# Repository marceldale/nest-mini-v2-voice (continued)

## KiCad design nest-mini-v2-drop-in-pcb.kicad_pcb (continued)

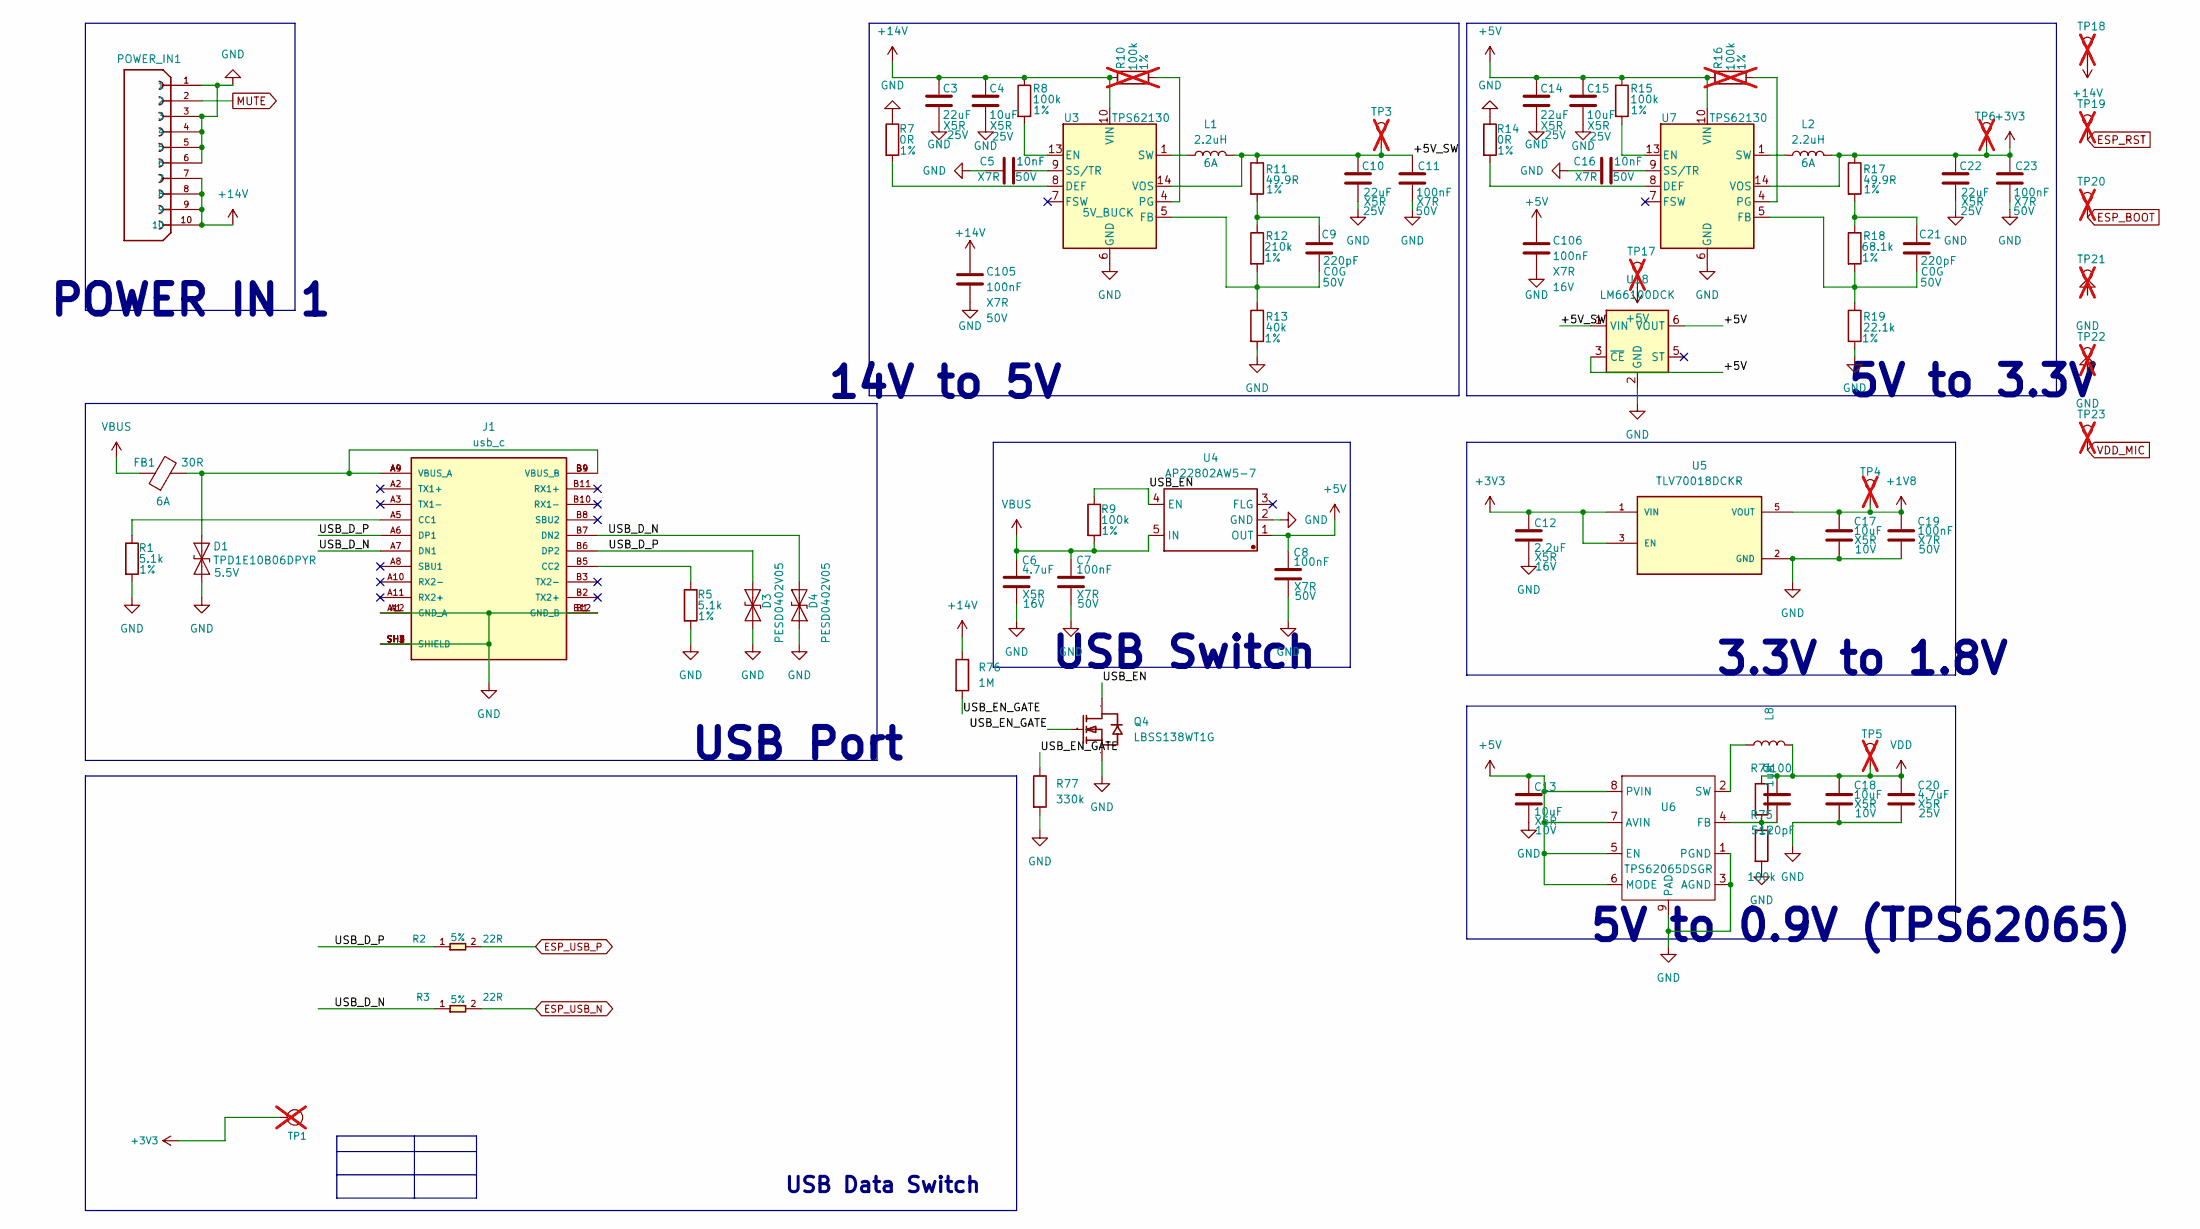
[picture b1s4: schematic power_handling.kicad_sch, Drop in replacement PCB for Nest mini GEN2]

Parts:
C3, C10, C14, C22: 22uF; C_0805_2012Metric; Voltage 25V; Manufacturer Part CL21A226MAQNNNE; LCSC Part # C45783
C4, C15: 10uF; C_0805_2012Metric; Voltage 25V; Manufacturer Part CL21A106KAYNNNE; LCSC Part # C15850
C5, C16: 10nF; C_0402_1005Metric; Voltage 50V; Manufacturer Part CL05B103KB5NNNC; LCSC Part # C15195
C6: 4.7uF; C_0603_1608Metric; Voltage 16V; Manufacturer Part CL10A475KO8NNNC; LCSC Part # C19666
C7, C8: 100nF; C_0603_1608Metric; Voltage 50V; Manufacturer Part CC0603KRX7R9BB104; LCSC Part # C14663
C9, C21: 220pF; C_0603_1608Metric; Voltage 50V; Manufacturer Part 0603CG221J500NT; LCSC Part # C156398
C11, C19, C23: 100nF; C_0805_2012Metric; Voltage 50V; Manufacturer Part CC0805KRX7R9BB104; LCSC Part # C49678
C12: 2.2uF; C_0603_1608Metric; Voltage 16V; Manufacturer Part CL10A225KO8NNNC; LCSC Part # C23630
C13, C17, C18: 10uF; C_0603_1608Metric; Voltage 10V; Manufacturer Part CL10A106KP8NNNC; LCSC Part # C19702
C20: 4.7uF; C_0805_2012Metric; Voltage 25V; Manufacturer Part CL21A475KAQNNNE; LCSC Part # C1779
C100: 120pF; C_0402_1005Metric; Voltage 50V; Manufacturer Part 0402CG121J500NT; LCSC Part # C40059
C105: 100nF; C_0402_1005Metric; Voltage 50V; Manufacturer Part CL05B104KB54PNC; LCSC Part # C307331
C106: 100nF; C_0402_1005Metric; Voltage 16V; Manufacturer Part CL05B104KO5NNNC; LCSC Part # C1525
D1: TPD1E10B06DPYR; TPD1E05U06DPYR; Voltage 5.5V; Manufacturer Part TPD1E10B06DPYR; LCSC Part # C48260
D3: PESD0402V05; D_0402_1005Metric; Part C19626254; LCSC Part # C19626254
D4: PESD0402V05; D_0402_1005Metric; Manufacturer Part PESD0402V05; LCSC Part # C19626254
FB1: 30R; R_0603_1608Metric; Part number BLM18PG300SN1D; LCSC Part # C17305
J1: usb_c; USB-C-SMD_TYPE-C-USB-18; Manufacturer Part 1054500101; LCSC Part # C134092
L1, L2: 2.2uH; L_Bourns_SRP4020TA; Manufacturer Part SRP4020TA-2R2M; LCSC Part # C719179
L8: 1uH; L_Murata_DFE201610P; Manufacturer Part WPN201610U1R0MTY01; LCSC Part # C395545
POWER_IN1: FH34SRJ-10S-0.5SH_50_; HRS_FH34SRJ-10S-0.5SH_50_; Manufacturer Part FH34SRJ-10S-0.5SH(50); LCSC Part # C324723
Q4: LBSS138WT1G; SOT-323_SC-70; Manufacturer Part LBSS138WT1G; LCSC Part # C383201
R1, R5: 5.1k; R_0402_1005Metric; Tolerance 1%; Manufacturer Part 0402WGF5101TCE; LCSC Part # C25905
R2, R3: 22R; R_0402_1005Metric; Tolerance 5%; MPN RC0402JR-0722RL; LCSC Part # C25092
R7, R14: 0R; R_0402_1005Metric; Tolerance 1%; Manufacturer Part 0402WGF0000TCE; LCSC Part # C17168
R8, R9, R15: 100k; R_0402_1005Metric; Tolerance 1%; Manufacturer Part 0402WGF1003TCE; LCSC Part # C25741
R10, R16: 100k; R_0402_1005Metric; Tolerance 1%; Manufacturer Part 0402WGJ0104TCE; LCSC Part # C25530; not fitted
R11, R17: 49.9R; R_0603_1608Metric; Tolerance 1%; Manufacturer Part 0603WAF499JT5E; LCSC Part # C23185
R12: 210k; R_0603_1608Metric; Tolerance 1%; Manufacturer Part 0603WAF2103T5E; LCSC Part # C22952
R13: 40k; R_0603_1608Metric; Tolerance 1%; Manufacturer Part RT0603BRD0740KL; LCSC Part # C861392
R18: 68.1k; R_0603_1608Metric; Tolerance 1%; Manufacturer Part 0603WAF6812T5E; LCSC Part # C25976
R19: 22.1k; R_0603_1608Metric; Tolerance 1%; Manufacturer Part 0603WAF2212T5E; LCSC Part # C25961
R74: 51k; R_0402_1005Metric; Manufacturer Part 0402WGF5102TCE; LCSC Part # C25794
R75: 100k; R_0402_1005Metric; Manufacturer Part 0402WGF1003TCE; LCSC Part # C25741
R76: 1M; R_0402_1005Metric; Manufacturer Part 0402WGF1004TCE; LCSC Part # C26083
R77: 330k; R_0402_1005Metric; Manufacturer Part 0402WGF3303TCE; LCSC Part # C25778
TP1, TP6: 3V3; TestPoint_Pad_D1.0mm; not fitted
TP3: 5V_SW; TestPoint_Pad_D1.0mm; not fitted
TP4: 1V8; TestPoint_Pad_D1.0mm; not fitted
TP5: VDD; TestPoint_Pad_D1.0mm; not fitted
TP17: 5V; TestPoint_Pad_D1.0mm; not fitted
TP18: 14V; TestPoint_Pad_D1.0mm; not fitted
TP19: RST; TestPoint_Pad_D1.0mm; not fitted
TP20: BOOT; TestPoint_Pad_D1.0mm; not fitted
TP21, TP22: GND; TestPoint_Pad_D1.0mm; not fitted
TP23: VMIC; TestPoint_Pad_D1.0mm; not fitted
U3, U7: TPS62130; VQFN-16-1EP_3x3mm_P0.5mm_EP1.68x1.68mm_ThermalVias; Manufacturer Part TPS62130ARGTR; LCSC Part # C337502
U4: AP22802AW5-7; SOT-23-5; Manufacturer Part AP22802AW5-7; LCSC Part # C211404
U5: TLV70018DCKR; SOT65P210X110-5N; PARTREV 3.1 - July 16, 2013; LCSC Part # C133796
U6: TPS62065DSGR; Texas_DSG0008A_WSON-8-1EP_2x2mm_P0.5mm_EP0.9x1.6mm; Manufacturer Part TPS62065DSGR; LCSC Part # C398352
U18: LM66100DCK; SOT-363_SC-70-6; Manufacturer Part LM66100DCKR; LCSC Part # C2869734

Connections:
+1V8: C17.1, C19.1, TP4.1, U5.5 (VOUT); also elsewhere on the board
+3V3: C12.1, C22.1, C23.1, L2.2, R17.1, TP1.1 (T), TP6.1, U5.1 (VIN), U5.3 (EN), U7.14 (VOS); also elsewhere on the board
+5V: C8.1, C13.1, C14.1, C15.1, C106.1, R15.1, R16.1, TP17.1, U4.1 (OUT), U6.5 (EN), U6.6 (MODE), U6.7 (AVIN), U6.8 (PVIN), U7.10 (VIN), U7.11 (VIN), U7.12 (VIN), U18.3 (~CE), U18.6 (VOUT); also elsewhere on the board
+14V: C3.1, C4.1, C105.1, POWER_IN1.7, POWER_IN1.8, POWER_IN1.9, POWER_IN1.10, R8.1, R10.1, R76.1, TP18.1, U3.10 (VIN), U3.11 (VIN), U3.12 (VIN); also elsewhere on the board
/Power/+5V_SW: C10.1, C11.1, L1.2, R11.1, TP3.1, U3.14 (VOS), U18.1 (VIN)
/Power/USB_D_N: D4.2 (A2), J1.A7 (DN1), J1.B7 (DN2), R3.1
/Power/USB_D_P: D3.2 (A2), J1.A6 (DP1), J1.B6 (DP2), R2.1
/Power/USB_EN: Q4.3 (D), R9.1, U4.4 (EN)
/Power/USB_EN_GATE: Q4.1 (G), R76.2, R77.1
ESP_BOOT: TP20.1; also elsewhere on the board
ESP_RST: TP19.1; also elsewhere on the board
ESP_USB_N: R3.2; also elsewhere on the board
ESP_USB_P: R2.2; also elsewhere on the board
GND: C3.2, C4.2, C5.1, C6.2, C7.2, C8.2, C10.2, C11.2, C12.2, C13.2, C14.2, C15.2, C16.1, C17.2, C18.2, C19.2, C20.2, C22.2, C23.2, C105.2, C106.2, D1.1 (A1), D3.1 (A1), D4.1 (A1), J1.A1 (GND_A), J1.A12 (GND_A), J1.B1 (GND_B), J1.B12 (GND_B), J1.SH1 (SHIELD), J1.SH2 (SHIELD), J1.SH3 (SHIELD), J1.SH4 (SHIELD), POWER_IN1.1, POWER_IN1.3, POWER_IN1.4, POWER_IN1.5, POWER_IN1.6, Q4.2 (S), R1.2, R5.2, R7.1, R13.2, R14.1, R19.2, R75.2, R77.2, TP21.1, TP22.1, U3.6 (GND), U3.15 (GND), U3.16 (GND), U3.17 (GND), U4.2 (GND), U5.2 (GND), U6.1 (PGND), U6.3 (AGND), U6.9 (PAD), U7.6 (GND), U7.15 (GND), U7.16 (GND), U7.17 (GND), U18.2 (GND); also elsewhere on the board
MUTE: POWER_IN1.2; also elsewhere on the board
unnamed: C9.1, R11.2, R12.1
unnamed: C21.1, R17.2, R18.1
unnamed: D1.2 (A2), FB1.2, J1.A4 (VBUS_A), J1.A9 (VBUS_A), J1.B4 (VBUS_B), J1.B9 (VBUS_B)
unnamed: J1.A5 (CC1), R1.1
unnamed: J1.B5 (CC2), R5.1
unnamed: L1.1, U3.1 (SW), U3.2 (SW), U3.3 (SW)
unnamed: L2.1, U7.1 (SW), U7.2 (SW), U7.3 (SW)
unnamed: R7.2, U3.8 (DEF)
unnamed: R8.2, U3.13 (EN)
unnamed: C9.2, R12.2, R13.1, U3.5 (FB)
unnamed: R10.2, U3.4 (PG)
unnamed: C5.2, U3.9 (SS/TR)
unnamed: C100.2, R74.2, R75.1, U6.4 (FB)
unnamed: L8.1, U6.2 (SW)
unnamed: R14.2, U7.8 (DEF)
unnamed: R15.2, U7.13 (EN)
unnamed: C21.2, R18.2, R19.1, U7.5 (FB)
unnamed: R16.2, U7.4 (PG)
unnamed: C16.2, U7.9 (SS/TR)
VBUS: C6.1, C7.1, FB1.1, R9.2, U4.5 (IN); also elsewhere on the board
VDD: C18.1, C20.1, C100.1, L8.2, R74.1, TP5.1; also elsewhere on the board
VDD_MIC: TP23.1; also elsewhere on the board

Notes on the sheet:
USB Port
POWER IN 1
14V to 5V
USB Switch
USB Data Switch
3.3V to 1.8V
5V to 3.3V
5V to 0.9V (TPS62065)

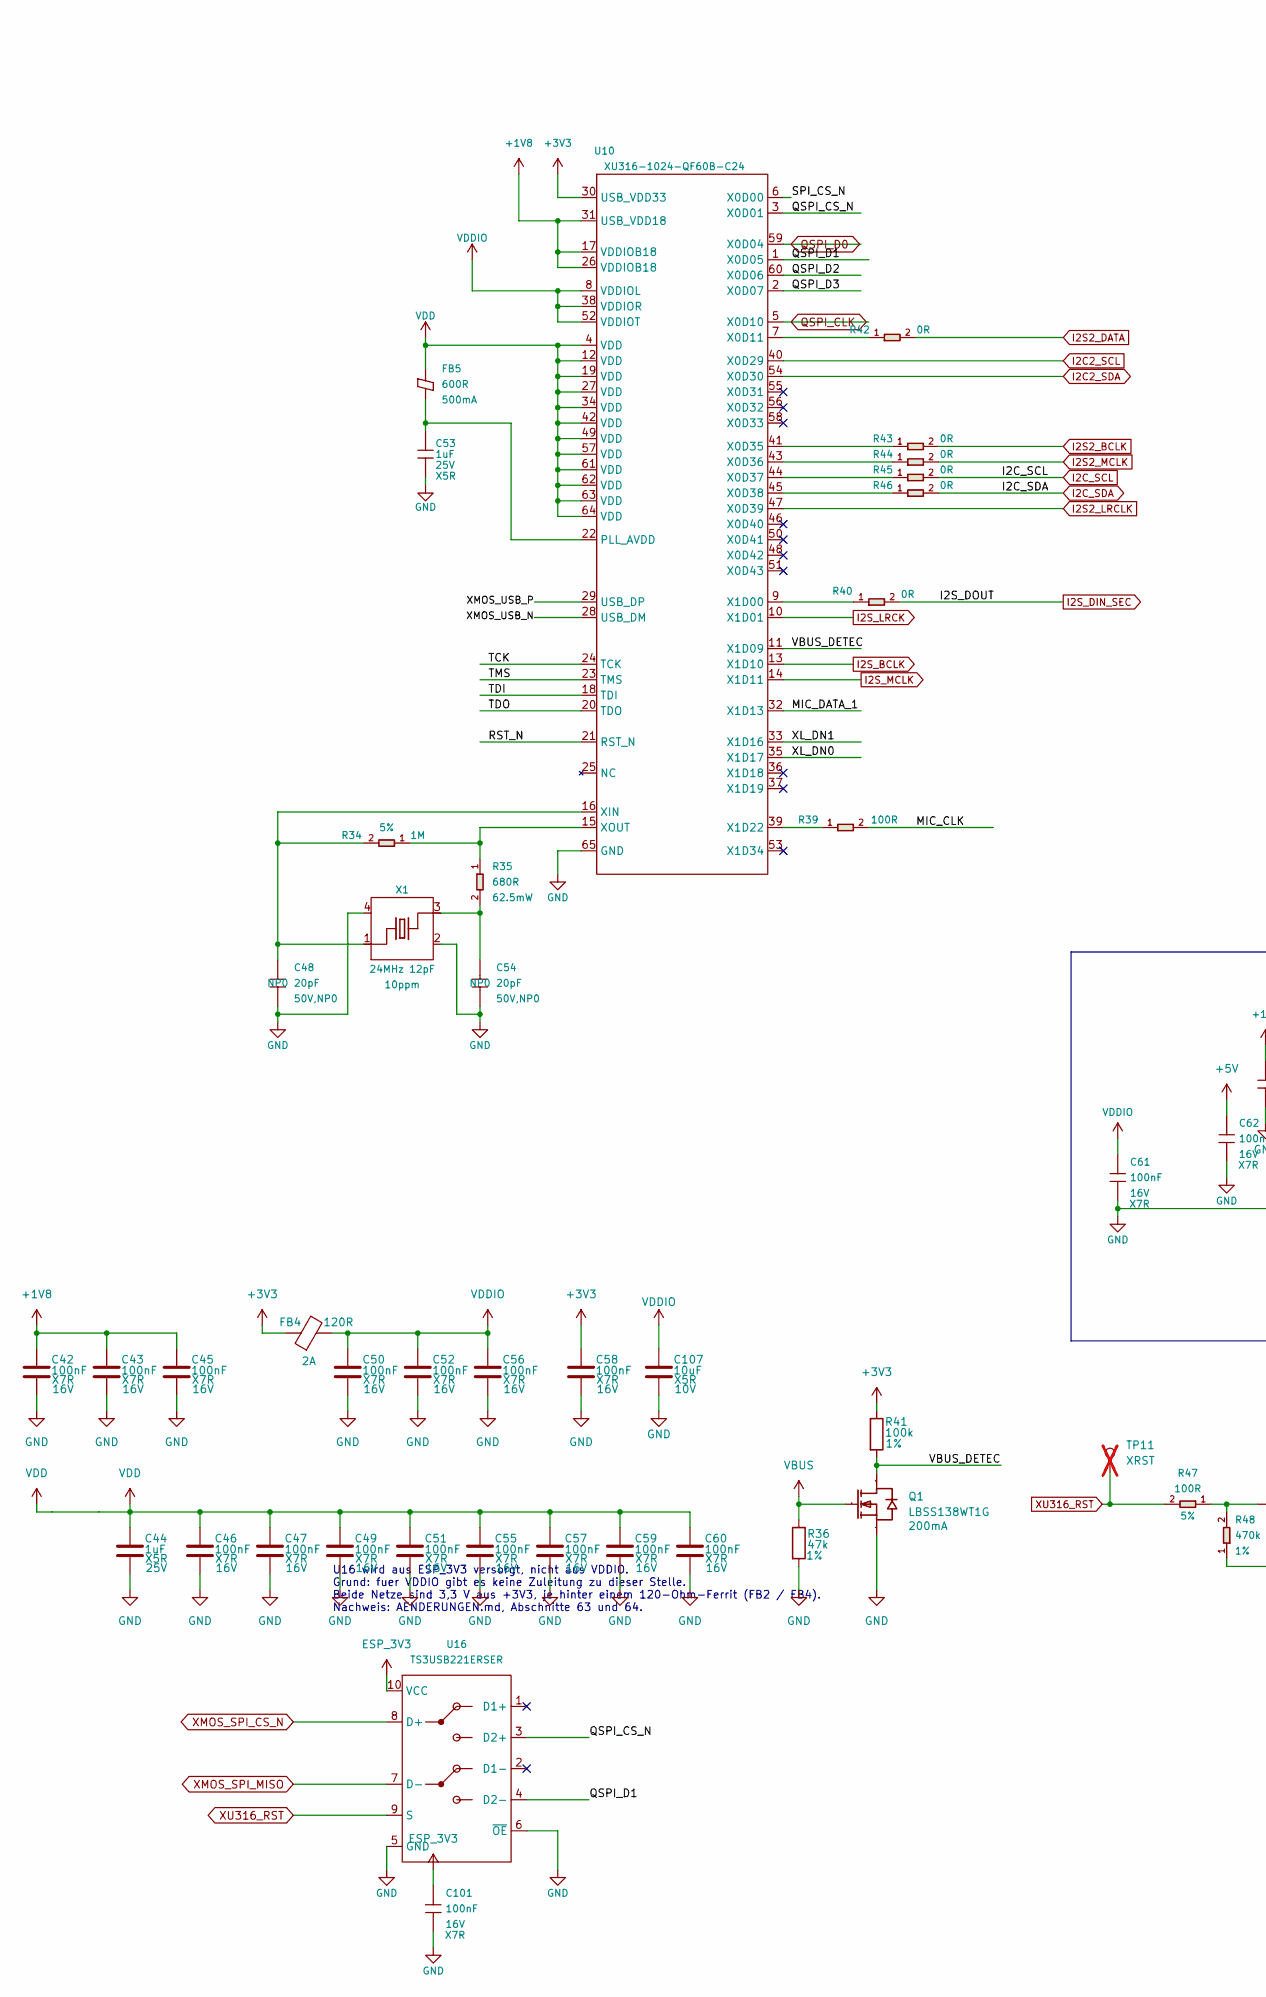
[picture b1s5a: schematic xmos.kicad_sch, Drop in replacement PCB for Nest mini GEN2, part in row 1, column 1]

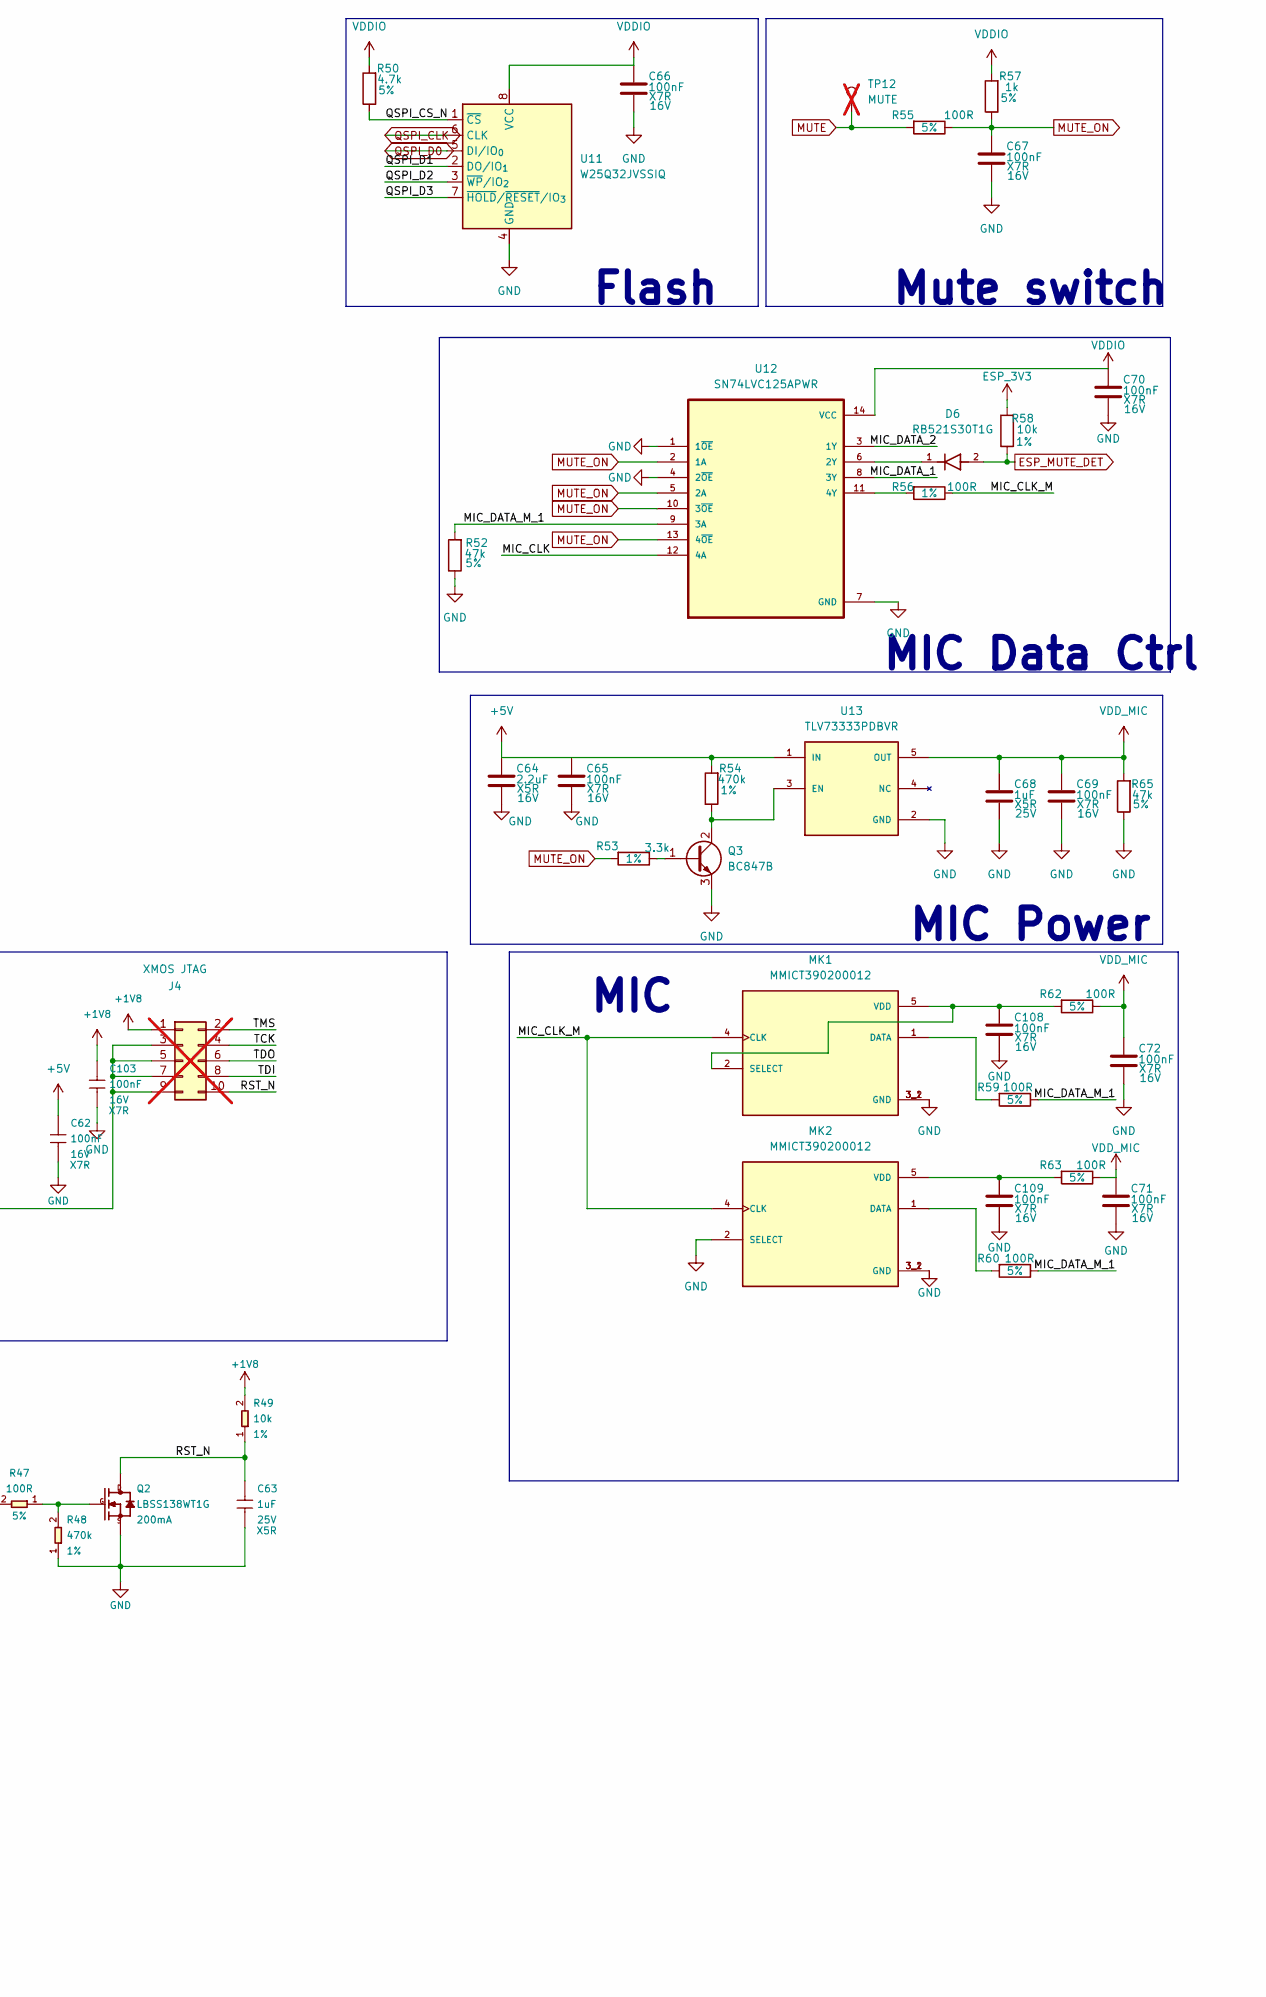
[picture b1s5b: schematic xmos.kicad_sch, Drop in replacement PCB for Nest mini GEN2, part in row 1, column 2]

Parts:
C42, C43, C45, C46, C47, C49, C50, C51, C52, C55, C56, C57, C58, C59, C60, C65, C66, C67, C69, C70, C71, C72, C108, C109: 100nF; C_0402_1005Metric; Voltage 16V; Manufacturer Part CL05B104KO5NNNC; LCSC Part # C1525
C44, C68: 1uF; C_0402_1005Metric; Voltage 25V; Manufacturer Part CL05A105KA5NQNC; LCSC Part # C52923
C48, C54: 20pF; C_0402_1005Metric; Voltage Rating 50V,NP0; Voltage 50V; MPN 0402CG200J500NT; LCSC Part # C1554
C53: 1uF; C_0402_1005Metric; Voltage Rating 25V; Voltage 25V; MPN CL05A105KA5NQNC; LCSC Part # C52923
C61, C62: 100nF; C_0402_1005Metric; Voltage Rating 16V; Voltage 16V; MPN CL05B104KO5NNNC; LCSC Part # C1525
C63: 1uF; C_0402_1005Metric; Voltage Rating 25V; MPN CL05A105KA5NQNC; LCSC Part # C52923
C64: 2.2uF; C_0603_1608Metric; Voltage 16V; Manufacturer Part CL10A225KO8NNNC; LCSC Part # C23630
C101, C103: 100nF; C_0402_1005Metric; Voltage Rating 16V; MPN CL05B104KO5NNNC; LCSC Part # C1525
C107: 10uF; C_0603_1608Metric; Voltage 10V; Manufacturer Part CL10A106KP8NNNC; LCSC Part # C19702
D6: RB521S30T1G; DIOM168X70N; PARTREV 7/11/1905; LCSC Part # C27636108
FB4: 120R; BLM18PG121SN1D; Part number BLM18AG121SN1D; LCSC Part # C14709
FB5: 600R; BLM18PG121SN1D; Rating 500mA; MPN BLM18KG601SN1D; LCSC Part # C85833
J4: XMOS JTAG; xSYS2_2x05_P1.27mm_Pads; not fitted
MK1, MK2: MMICT390200012; MIC_T3902; PARTREV 1.0; LCSC Part # C3171752
Q1: LBSS138WT1G; SC-70-3_L2.1-W1.3-P0.65-LS2.1-BR; Manufacturer Part LBSS138WT1G; LCSC Part # C383201
Q2: LBSS138WT1G; SOT-323_SC-70; Rating 200mA; MPN LBSS138WT1G; LCSC Part # C383201
Q3: BC847B; SOT-23; Manufacturer Part BC847B; LCSC Part # C20069135
R34: 1M; R_0402_1005Metric; Power Rating 5%; MPN 0402WGF1004TCE; LCSC Part # C26083
R35: 680R; R_0402_1005Metric; Power Rating 62.5mW; MPN CR0402FF6800G; LCSC Part # C100510
R36: 47k; R_0402_1005Metric; Tolerance 1%; Manufacturer Part 0402WGF4702TCE; LCSC Part # C25792
R39: 100R; R_0402_1005Metric; Power Rating 5%; MPN 0402WGF1000TCE; LCSC Part # C25076
R40, R43, R44, R45, R46: 0R; R_0402_1005Metric; Power Rating 5%; MPN 0402WGF0000TCE; LCSC Part # C17168
R41: 100k; R_0402_1005Metric; Tolerance 1%; Manufacturer Part 0402WGF1003TCE; LCSC Part # C25741
R42: 0R; R_0402_1005Metric; Tolerance 5%; MPN 0402WGF0000TCE; LCSC Part # C17168
R47: 100R; R_0402_1005Metric; Power Rating 5%; MPN RC0402JR-07100RL; LCSC Part # C25076
R48: 470k; R_0402_1005Metric; Power Rating 1%; MPN RC0402FR-07470KL; LCSC Part # C25790
R49: 10k; R_0402_1005Metric; Power Rating 1%; MPN RC0402FR-0710KL; LCSC Part # C25744
R50: 4.7k; R_0402_1005Metric; Tolerance 5%; Manufacturer Part 0402WGF4701TCE; LCSC Part # C25900
R52, R65: 47k; R_0402_1005Metric; Tolerance 5%; Manufacturer Part 0402WGF4702TCE; LCSC Part # C25792
R53: 3.3k; R_0402_1005Metric; Tolerance 1%; Manufacturer Part 0402WGF3301TCE; LCSC Part # C25890
R54: 470k; R_0402_1005Metric; Tolerance 1%; Manufacturer Part 0402WGF4703TCE; LCSC Part # C25790
R55, R59, R60, R62, R63: 100R; R_0402_1005Metric; Tolerance 5%; Manufacturer Part 0402WGF1000TCE; LCSC Part # C25076
R56: 100R; R_0402_1005Metric; Tolerance 1%; Manufacturer Part 0402WGF1000TCE; LCSC Part # C25076
R57: 1k; R_0402_1005Metric; Tolerance 5%; Manufacturer Part 0402WGF1001TCE; LCSC Part # C11702
R58: 10k; R_0402_1005Metric; Tolerance 1%; Manufacturer Part 0402WGF1002TCE; LCSC Part # C25744
TP11: XRST; TestPoint_Pad_D1.0mm; not fitted
TP12: MUTE; TestPoint_Pad_D1.0mm; not fitted
U10: XU316-1024-QF60B-C24; MPN XU316-1024-QF60B-C24; LCSC Part # C6617472
U11: W25Q32JVSSIQ; SOIC-8_5.3x5.3mm_P1.27mm; Manufacturer Part W25Q32JVSSIQ; LCSC Part # C179173
U12: SN74LVC125APWR; SOP65P640X120-14N; Manufacturer Part SN74LVC125APWR; LCSC Part # C7813
U13: TLV73333PDBVR; PARTREV C; LCSC Part # C134139
U16: TS3USB221ERSER; MPN TS3USB221ERSER; LCSC Part # C129313
X1: 24MHz 12pF; X4-SMD-2.0X1.6MM; Rating 10ppm; MPN 7F24000E12UCG; LCSC Part # C252273

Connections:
+1V8: C42.1, C43.1, C45.1, C103.1, J4.1, R49.2, U10.17 (VDDIOB18), U10.26 (VDDIOB18), U10.31 (USB_VDD18); also elsewhere on the board
+3V3: C58.1, FB4.1, R41.1, U10.30 (USB_VDD33); also elsewhere on the board
+5V: C62.1, C64.1, C65.1, R54.2, U13.1 (IN); also elsewhere on the board
/XMOS/MIC_CLK: R39.2, U12.12 (4A)
/XMOS/MIC_CLK_M: MK1.4 (CLK), MK2.4 (CLK), R56.1
/XMOS/MIC_DATA_1: U10.32 (X1D13), U12.8 (3Y)
/XMOS/MIC_DATA_2: U12.3 (1Y)
/XMOS/MIC_DATA_M_1: R52.2, R59.1, R60.1, U12.9 (3A)
/XMOS/QSPI_CS_N: R50.1, U10.3 (X0D01), U11.1 (~CS), U16.3 (D2+)
/XMOS/QSPI_D1: U10.1 (X0D05), U11.2 (DO/IO_{1}), U16.4 (D2-)
/XMOS/QSPI_D2: U10.60 (X0D06), U11.3 (~WP/IO_{2})
/XMOS/QSPI_D3: U10.2 (X0D07), U11.7 (~HOLD/~RESET/IO_{3})
/XMOS/RST_N: C63.1, J4.10, Q2.3 (D), R49.1, U10.21 (RST_N)
/XMOS/SPI_CS_N: U10.6 (X0D00)
/XMOS/TCK: J4.4, U10.24 (TCK)
/XMOS/TDI: J4.8, U10.18 (TDI)
/XMOS/TDO: J4.6, U10.20 (TDO)
/XMOS/TMS: J4.2, U10.23 (TMS)
/XMOS/VBUS_DETEC: Q1.3 (D), R41.2, U10.11 (X1D09)
/XMOS/XL_DN0: U10.35 (X1D17)
/XMOS/XL_DN1: U10.33 (X1D16)
/XMOS/XMOS_USB_N: U10.28 (USB_DM)
/XMOS/XMOS_USB_P: U10.29 (USB_DP)
ESP_3V3: C101.1, R58.2, U16.10 (VCC); also elsewhere on the board
ESP_MUTE_DET: D6.2, R58.1; also elsewhere on the board
GND: C42.2, C43.2, C44.2, C45.2, C46.2, C47.2, C48.2, C49.2, C50.2, C51.2, C52.2, C53.2, C54.2, C55.2, C56.2, C57.2, C58.2, C59.2, C60.2, C61.2, C62.2, C63.2, C64.2, C65.2, C66.2, C67.2, C68.2, C69.2, C70.2, C71.2, C72.2, C101.2, C103.2, C107.2, C108.2, C109.2, J4.3, J4.5, J4.7, J4.9, MK1.3_1 (GND), MK1.3_2 (GND), MK2.2 (SELECT), MK2.3_1 (GND), MK2.3_2 (GND), Q1.2 (S), Q2.2 (S), Q3.3 (E), R36.2, R48.1, R52.1, R65.1, U10.65 (GND), U11.4 (GND), U12.1 (1~OE), U12.4 (2~OE), U12.7 (GND), U13.2 (GND), U16.5 (GND), U16.6 (~OE), X1.2, X1.4; also elsewhere on the board
I2C2_SCL: U10.40 (X0D29)
I2C2_SDA: U10.54 (X0D30)
I2C_SCL: R45.2; also elsewhere on the board
I2C_SDA: R46.2; also elsewhere on the board
I2S2_BCLK: R43.2; also elsewhere on the board
I2S2_DATA: R42.2; also elsewhere on the board
I2S2_LRCLK: U10.47 (X0D39); also elsewhere on the board
I2S2_MCLK: R44.2; also elsewhere on the board
I2S_BCLK: U10.13 (X1D10); also elsewhere on the board
I2S_DIN_SEC: R40.2; also elsewhere on the board
I2S_LRCK: U10.10 (X1D01); also elsewhere on the board
I2S_MCLK: U10.14 (X1D11); also elsewhere on the board
MUTE: R55.2, TP12.1; also elsewhere on the board
MUTE_ON: C67.1, R53.2, R55.1, R57.1, U12.2 (1A), U12.5 (2A), U12.10 (3~OE), U12.13 (4~OE)
unnamed: C54.1, R35.2, X1.3
unnamed: MK1.1 (DATA), R59.2
unnamed: C108.1, MK1.2 (SELECT), MK1.5 (VDD), R62.2
unnamed: MK2.1 (DATA), R60.2
unnamed: C109.1, MK2.5 (VDD), R63.2
unnamed: Q2.1 (G), R47.1, R48.2
unnamed: Q3.1 (B), R53.1
unnamed: Q3.2 (C), R54.1, U13.3 (EN)
unnamed: C53.1, FB5.1, U10.22 (PLL_AVDD)
unnamed: R42.1, U10.7 (X0D11)
unnamed: R43.1, U10.41 (X0D35)
unnamed: R44.1, U10.43 (X0D36)
unnamed: R45.1, U10.44 (X0D37)
unnamed: R46.1, U10.45 (X0D38)
unnamed: R40.1, U10.9 (X1D00)
unnamed: R39.1, U10.39 (X1D22)
unnamed: C48.1, R34.2, U10.16 (XIN), X1.1
unnamed: R34.1, R35.1, U10.15 (XOUT)
unnamed: D6.1, U12.6 (2Y)
unnamed: R56.2, U12.11 (4Y)
QSPI_CLK: U10.5 (X0D10), U11.6 (CLK); also elsewhere on the board
QSPI_D0: U10.59 (X0D04), U11.5 (DI/IO_{0}); also elsewhere on the board
VBUS: Q1.1 (G), R36.1; also elsewhere on the board
VDD: C44.1, C46.1, C47.1, C49.1, C51.1, C55.1, C57.1, C59.1, C60.1, FB5.2, U10.4 (VDD), U10.12 (VDD), U10.19 (VDD), U10.27 (VDD), U10.34 (VDD), U10.42 (VDD), U10.49 (VDD), U10.57 (VDD), U10.61 (VDD), U10.62 (VDD), U10.63 (VDD), U10.64 (VDD); also elsewhere on the board
VDDIO: C50.1, C52.1, C56.1, C61.1, C66.1, C70.1, C107.1, FB4.2, R50.2, R57.2, U10.8 (VDDIOL), U10.38 (VDDIOR), U10.52 (VDDIOT), U11.8 (VCC), U12.14 (VCC)
VDD_MIC: C68.1, C69.1, C71.1, C72.1, R62.1, R63.1, R65.2, U13.5 (OUT); also elsewhere on the board
XMOS_SPI_CS_N: U16.8 (D+); also elsewhere on the board
XMOS_SPI_MISO: U16.7 (D-); also elsewhere on the board
XU316_RST: R47.2, TP11.1, U16.9 (S); also elsewhere on the board

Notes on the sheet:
Flash
MIC
Mute switch
MIC Power
MIC Data Ctrl
U16 wird aus ESP_3V3 versorgt, nicht aus VDDIO. Grund: fuer VDDIO gibt es keine Zuleitung zu dieser Stelle. Beide Netze sind 3,3 V aus +3V3, je hinter einem 120-Ohm-Ferrit (FB2 / FB4). Nachweis: AENDERUNGEN.md, Abschnitte 63 und 64.

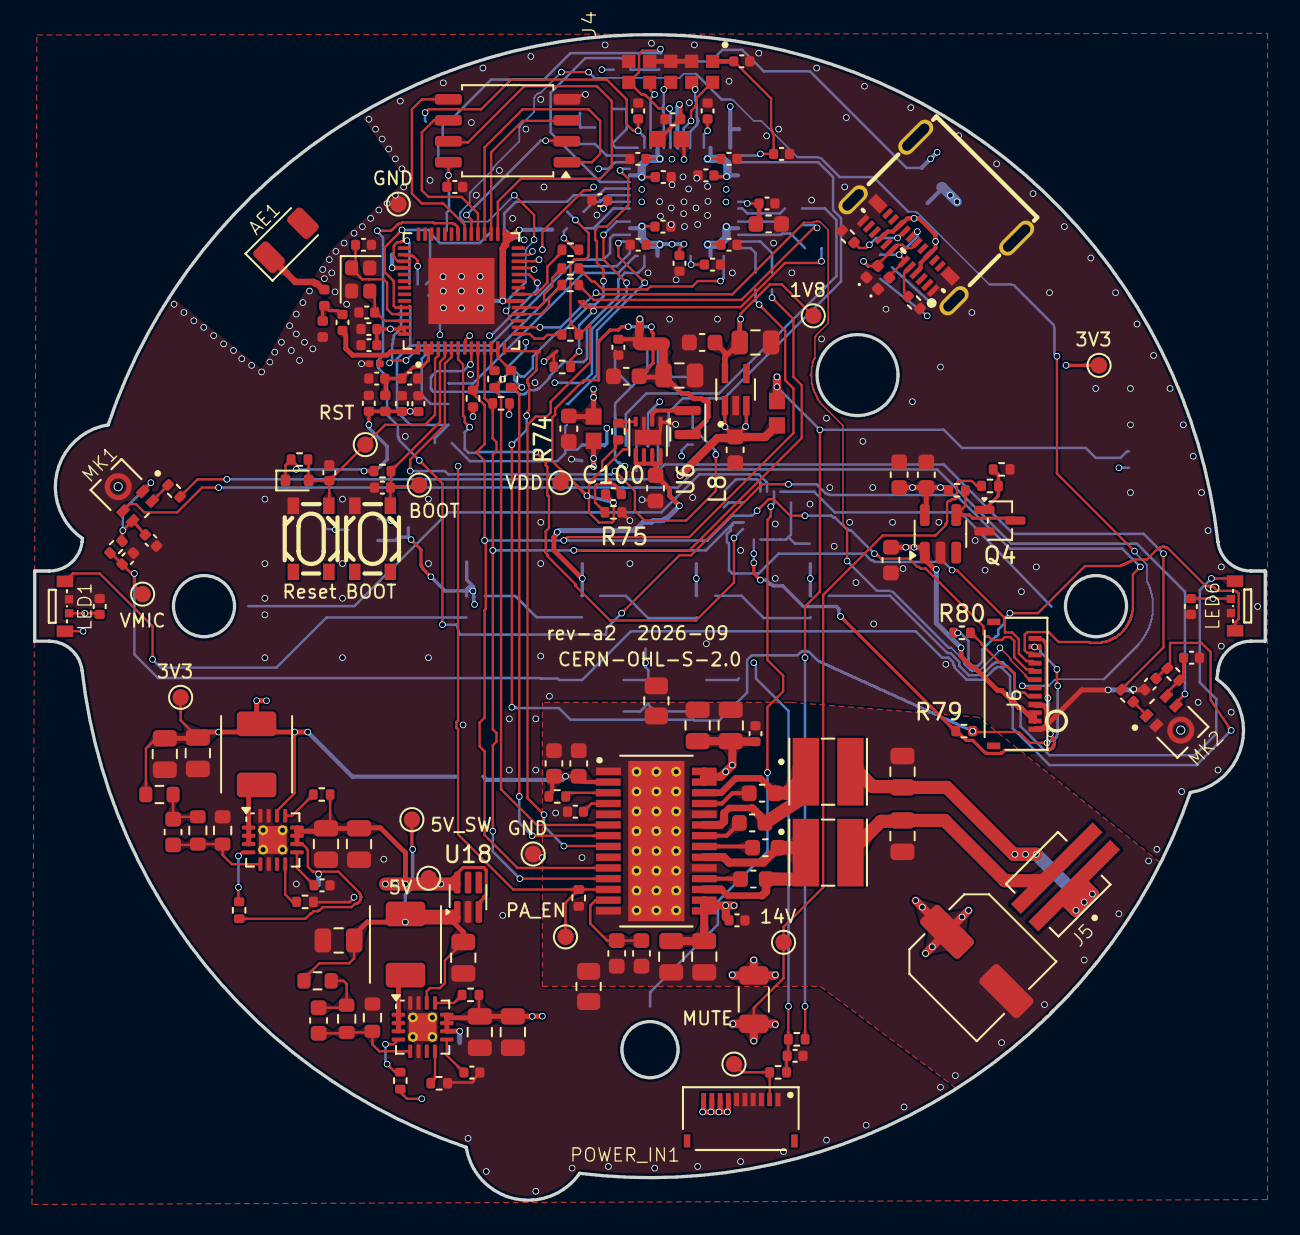
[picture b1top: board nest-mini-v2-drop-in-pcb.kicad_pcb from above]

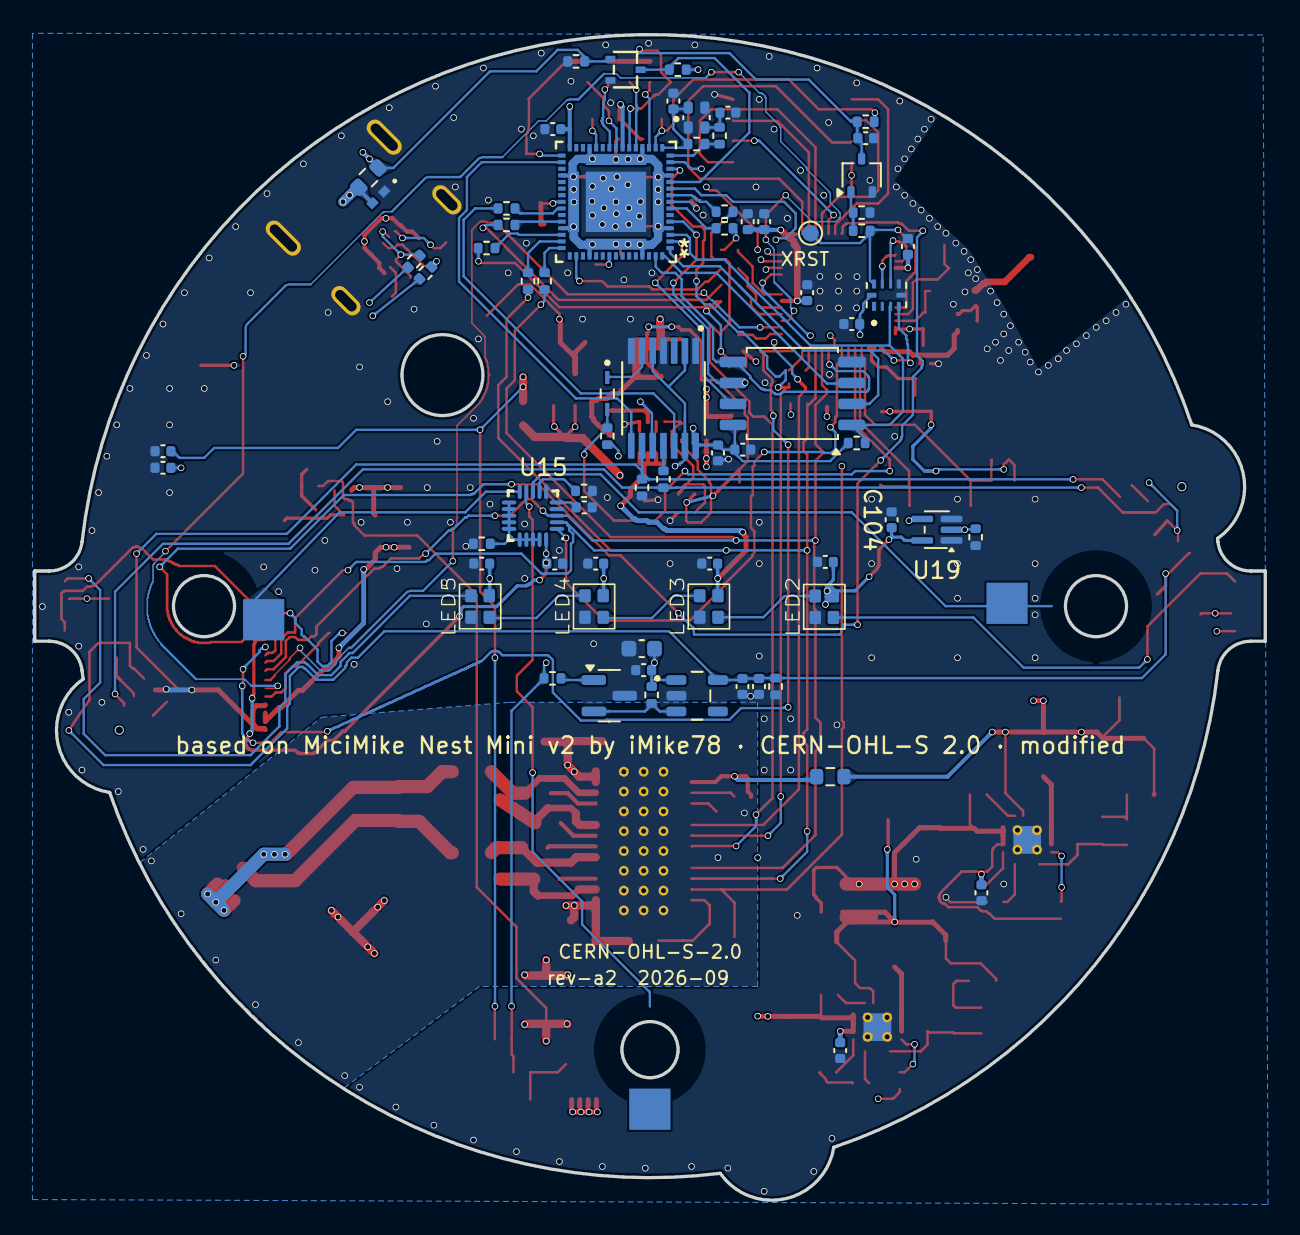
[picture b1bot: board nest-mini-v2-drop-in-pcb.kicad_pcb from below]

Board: 4 copper layers, 74.5 x 70.6 mm, 249 parts (75 on the bottom side), 143 nets.

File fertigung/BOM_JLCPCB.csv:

Comment,Designator,Footprint,LCSC Part #
2450AT18A100E,AE1,Johanson_2450AT18x100,C89334
22uF,"C3,C10,C14,C22,C79,C81,C84,C85",C_0805_2012Metric,C45783
10uF,"C4,C15",C_0805_2012Metric,C15850
10nF,"C5,C16",C_0402_1005Metric,C15195
4.7uF,"C6,C80,C90",C_0603_1608Metric,C19666
100nF,"C7,C8,C25,C82,C91",C_0603_1608Metric,C14663
220pF,"C9,C21",C_0603_1608Metric,C156398
100nF,"C11,C19,C23",C_0805_2012Metric,C49678
2.2uF,"C12,C64",C_0603_1608Metric,C23630
10uF,"C13,C17,C18,C107",C_0603_1608Metric,C19702
4.7uF,C20,C_0805_2012Metric,C1779
1uF,"C24,C31,C35,C39,C44,C53,C63,C68,C78",C_0402_1005Metric,C52923
12pF,"C26,C27,C29",C_0402_1005Metric,C1547
1.2pF,C28,C_0402_1005Metric,C327292
100nF,"C30,C32,C33,C34,C37,C38,C41,C42,C43,C45,C46,C47,C49,C50,C51,C52,C55,C56,C57,C58,C59,C60,C61,C62,C65,C66,C67,C69,C70,C71,C72,C92,C93,C94,C95,C96,C97,C98,C99,C101,C103,C104,C106,C108,C109",C_0402_1005Metric,C1525
2.4pF,C36,C_0402_1005Metric,C48346
10uF,C40,C_0402_1005Metric,C15525
20pF,"C48,C54",C_0402_1005Metric,C1554
0.22uF,"C74,C75,C76,C77",C_0603_1608Metric,C107083
100nF,"C83,C88,C105",C_0402_1005Metric,C307331
0.68uF,"C86,C87",C_0805_2012Metric,C107133
220uF,C89,C_Elec_6.3x7.7,C46550464
120pF,C100,C_0402_1005Metric,C40059
TPD1E10B06DPYR,D1,TPD1E05U06DPYR,C48260
PESD0402V05,"D3,D4",D_0402_1005Metric,C19626254
LRB520S-30T1G,D5,D_SOD-523,C83680
RB521S30T1G,D6,DIOM168X70N,C27636108
30R,FB1,R_0603_1608Metric,C17305
120R,"FB2,FB4",BLM18PG121SN1D,C14709
600R,FB5,BLM18PG121SN1D,C85833
usb_c,J1,USB-C-SMD_TYPE-C-USB-18,C134092
1775443-2,J5,1775443-2,C5162845
FH34SRJ-12S-0.5SH(50),J6,HRS_FH34SRJ-12S-0.5SH_50_,C424659
2.2uH,"L1,L2",L_Bourns_SRP4020TA,C719179
3.3nH,L3,L_0402_1005Metric,C16526
2.7nH,L4,L_0402_1005Metric,C434826
2.2nH,L5,L_0402_1005Metric,C162540
10uH,"L6,L7",MTQH404030S100MBT,C51883185
1uH,L8,L_Murata_DFE201610P,C395545
SK6812D-EC3210R,"LED1,LED6",LED-SMD_4P_SK6812D-EC3210R,C2890041
SK6812-EC20,"LED2,LED3,LED4,LED5",SK6805-EC20,C2909058
MMICT390200012,"MK1,MK2",MIC_T3902,C3171752
FH34SRJ-10S-0.5SH_50_,POWER_IN1,HRS_FH34SRJ-10S-0.5SH_50_,C324723
LBSS138WT1G,"Q1,Q2,Q4",SC-70-3_L2.1-W1.3-P0.65-LS2.1-BR / SOT-323_SC-70,C383201
BC847B,Q3,SOT-23,C20069135
5.1k,"R1,R5",R_0402_1005Metric,C25905
22R,"R2,R3",R_0402_1005Metric,C25092
0R,"R7,R14,R22,R24,R27,R28,R29,R30,R31,R40,R42,R43,R44,R45,R46",R_0402_1005Metric,C17168
100k,"R8,R9,R15,R41,R75",R_0402_1005Metric,C25741
49.9R,"R11,R17",R_0603_1608Metric,C23185
210k,R12,R_0603_1608Metric,C22952
40k,R13,R_0603_1608Metric,C861392
68.1k,R18,R_0603_1608Metric,C25976
22.1k,R19,R_0603_1608Metric,C25961
10k,"R20,R21,R49,R58,R79,R81",R_0402_1005Metric,C25744
4.7k,"R32,R33,R50,R70",R_0402_1005Metric,C25900
1M,"R34,R73,R76",R_0402_1005Metric,C26083
680R,R35,R_0402_1005Metric,C100510
47k,"R36,R52,R65,R71",R_0402_1005Metric,C25792
100R,"R39,R47,R55,R56,R59,R60,R62,R63,R80",R_0402_1005Metric,C25076
470k,"R48,R54",R_0402_1005Metric,C25790
3.3k,R53,R_0402_1005Metric,C25890
1k,R57,R_0402_1005Metric,C11702
0R,R66,R_1206_3216Metric,C17888
0R,R67,R_0603_1608Metric,C21189
0R,"R68,R69",R_0805_2012Metric,C17477
75k,R72,R_0402_1005Metric,C25798
51k,R74,R_0402_1005Metric,C25794
330k,R77,R_0402_1005Metric,C25778
Reset / BOOT,"SW1,SW2",SW-SMD_4P-L4.2-W3.2-P2.15-LS4.5,C221897
TPS62130,"U3,U7",VQFN-16-1EP_3x3mm_P0.5mm_EP1.68x1.68mm_ThermalVias,C337502
AP22802AW5-7,U4,SOT-23-5,C211404
TLV70018DCKR,U5,SOT65P210X110-5N,C133796
TPS62065DSGR,U6,Texas_DSG0008A_WSON-8-1EP_2x2mm_P0.5mm_EP0.9x1.6mm,C398352
ESP32-S3R8,U8,QFN40P700X700X90-57N,C2913194
W25Q128JVSIQ,U9,SOIC-8_5.3x5.3mm_P1.27mm,C97521
XU316-1024-QF60B-C24,U10,XU316-1024-QF60B-C24,C6617472
W25Q32JVSSIQ,U11,SOIC-8_5.3x5.3mm_P1.27mm,C179173
SN74LVC125APWR,U12,SOP65P640X120-14N,C7813
TLV73333PDBVR,U13,TLV73333PDBVR,C134139
TAS5805MPWPR,U14,TAS5805MPWPR,C478472
MPR121QR2,U15,MPR121QR2,C91322
TS3USB221ERSER,U16,TS3USB221ERSER,C129313
LM66100DCK,U18,SOT-363_SC-70-6,C2869734
74AHCT1G125,U19,SOT-353_SC-70-5,C12495
24MHz 12pF,X1,X4-SMD-2.0X1.6MM,C252273
40MHz,Y1,Crystal_SMD_2016-4Pin_2.0x1.6mm,C49158179
